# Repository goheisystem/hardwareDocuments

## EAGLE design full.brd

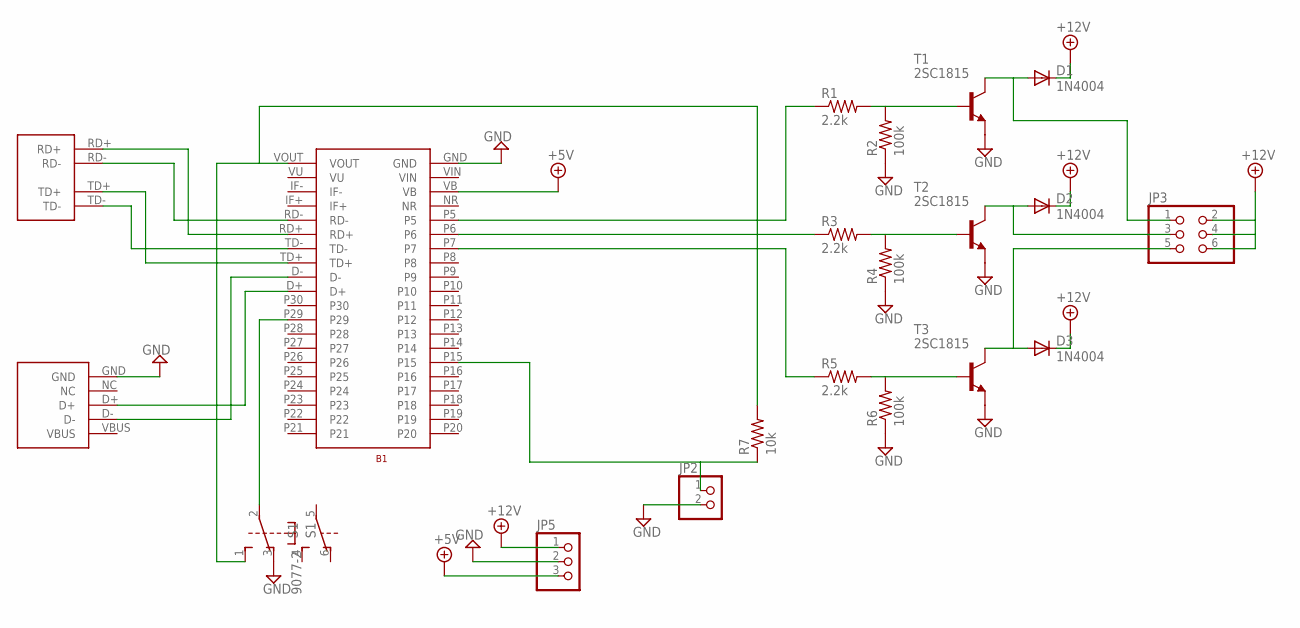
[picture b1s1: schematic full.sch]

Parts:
B1: MBED_LPC1768
D1, D2, D3: 1N4004; DO41-10
JP2: PINHD-1X2; 1X02
JP3: PINHD-2X3; 2X03
JP5: PINHD-1X3; 1X03
R1, R3, R5: 2.2k; 0204/7
R2, R4, R6: 100k; 0204/7
R7: 10k; 0204/7
RJ45_DIP1: AKIZUKI_RJ45_DIP
S1: 9077-2
T1, T2, T3: 2SC1815; TO92-ECB
USB_B1: AKIZUKI_MINI_USB_DIP

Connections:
+5V: B1.VB, JP5.3
+12V: D1.C, D2.C, D3.C, JP3.2, JP3.4, JP3.6, JP5.1
GND: B1.GND, JP2.2, JP5.2, R2.1, R4.1, R6.1, S1.3 (O), T1.E, T2.E, T3.E, USB_B1.GND
unnamed: R1.2, R2.2, T1.B
unnamed: R3.2, R4.2, T2.B
unnamed: R5.2, R6.2, T3.B
unnamed: B1.P6, R3.1
unnamed: B1.P5, R1.1
unnamed: B1.P7, R5.1
unnamed: D1.A, JP3.1, T1.C
unnamed: D2.A, JP3.3, T2.C
unnamed: D3.A, JP3.5, T3.C
unnamed: B1.RD-, RJ45_DIP1.RD-
unnamed: B1.RD+, RJ45_DIP1.RD+
unnamed: B1.TD+, RJ45_DIP1.TD+
unnamed: B1.TD-, RJ45_DIP1.TD-
unnamed: B1.D+, USB_B1.D+
unnamed: B1.D-, USB_B1.D-
unnamed: B1.P15, JP2.1, R7.1
unnamed: B1.VOUT, R7.2, S1.1 (S)
VBUS: USB_B1.VBUS
VIN: B1.VIN
VU: B1.VU

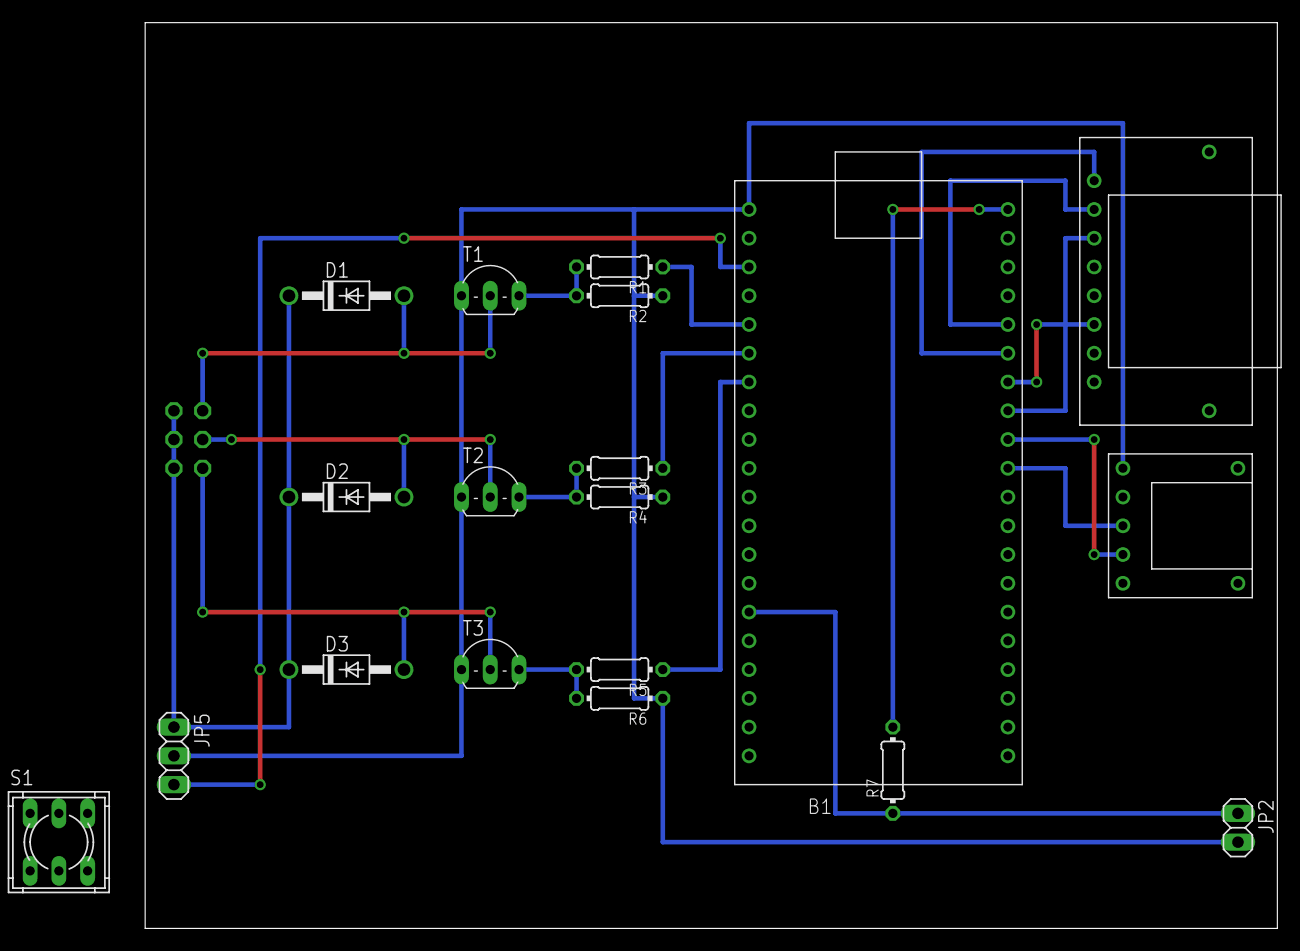
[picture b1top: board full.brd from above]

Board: 2 copper layers, 100.0 x 80.0 mm, 20 parts (1 on the bottom side), 20 nets.

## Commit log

2016-12-07 スイッチ追加
